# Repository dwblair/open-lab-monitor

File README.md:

open-lab-monitor
=================

### Overview

An open hardware microcontroller device for use in research and teaching laboratory settings, and as an independent sensing node.

### PCB

- Nice reference for MAGJACK options:
http://mbed.org/cookbook/Ethernet-RJ45 
- Nice reference for uSD breakout schematic, adafruit:
https://raw.github.com/adafruit/MicroSD-breakout-board/master/usdbreakout.png

### Code

Code for controlling the Open Lab Monitor device, the development and goals and applications of which are documented [here](https://github.com/Pioneer-Valley-Open-Science/pioneer-valley-open-science.github.com/issues/8).

The code consists of Arduino code to be loaded on an Arduino-based sensor platform, as well as a Processing and Python interface for interacting with the platform (e.g. plotting sensor values, downloading data as a CSV file). 

#### Notes on the Arduino Code

Some non-standard Arduino libraries are required, frozen versions of which can be found [here](https://github.com/dwblair/open-lab-monitor/tree/master/arduino/libraries).  Copy (or better yet, link) the folders under "libraries" to your "libraries" folder for your Arduino sketchbook:

* ThermistorLib (cversek's library for reading thermistor values) -- latest version found [here](https://github.com/cversek/umass-physics/tree/master/teis/arduino/ThermistorLib).
                                                                  
* SerialCommand (originally Steven Cogswell's slick library for parsing commands over serial)  -- check out his surly [blog post](http://husks.wordpress.com/2011/05/23/a-minimal-arduino-library-for-processing-serial-commands/); we are using the new and improved version hosted on github [here](https://github.com/kroimon/Arduino-SerialCommand)

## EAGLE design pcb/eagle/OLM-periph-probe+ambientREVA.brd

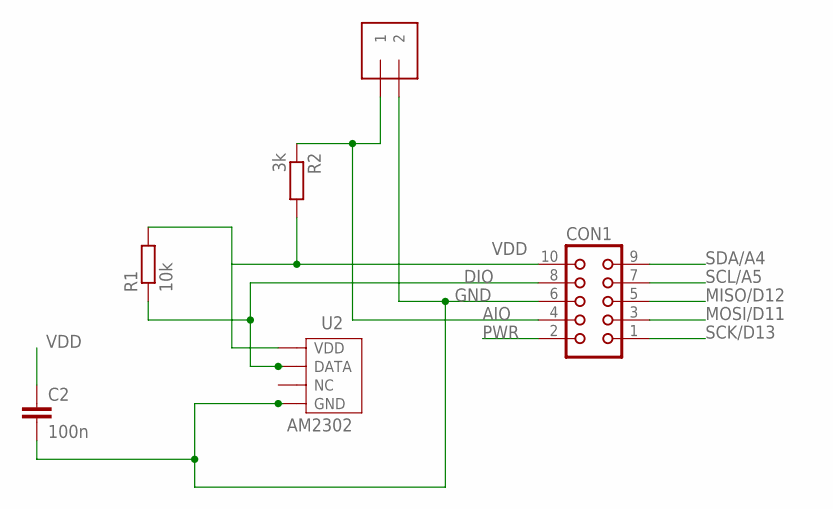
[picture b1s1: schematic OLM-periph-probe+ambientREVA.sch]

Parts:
C2: 100n; C025-024X044
CON1: CON10L
J1: 1X2-3.5MM
R1: 10k; 0204/7
R2: 3k; 0204/7
U2: AM2302

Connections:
AIO: CON1.4, J1.1, R2.1
DIO: CON1.8, R1.1, U2.P$2 (DATA)
GND: C2.2, CON1.6, J1.2, U2.P$4 (GND)
MISO/D12: CON1.5
MOSI/D11: CON1.3
PWR: CON1.2
SCK/D13: CON1.1
SCL/A5: CON1.7
SDA/A4: CON1.9
VDD: C2.1, CON1.10, R1.2, R2.2, U2.P$1 (VDD)

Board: 2 copper layers, 6 parts (0 on the bottom side), 4 nets, no tracks yet.

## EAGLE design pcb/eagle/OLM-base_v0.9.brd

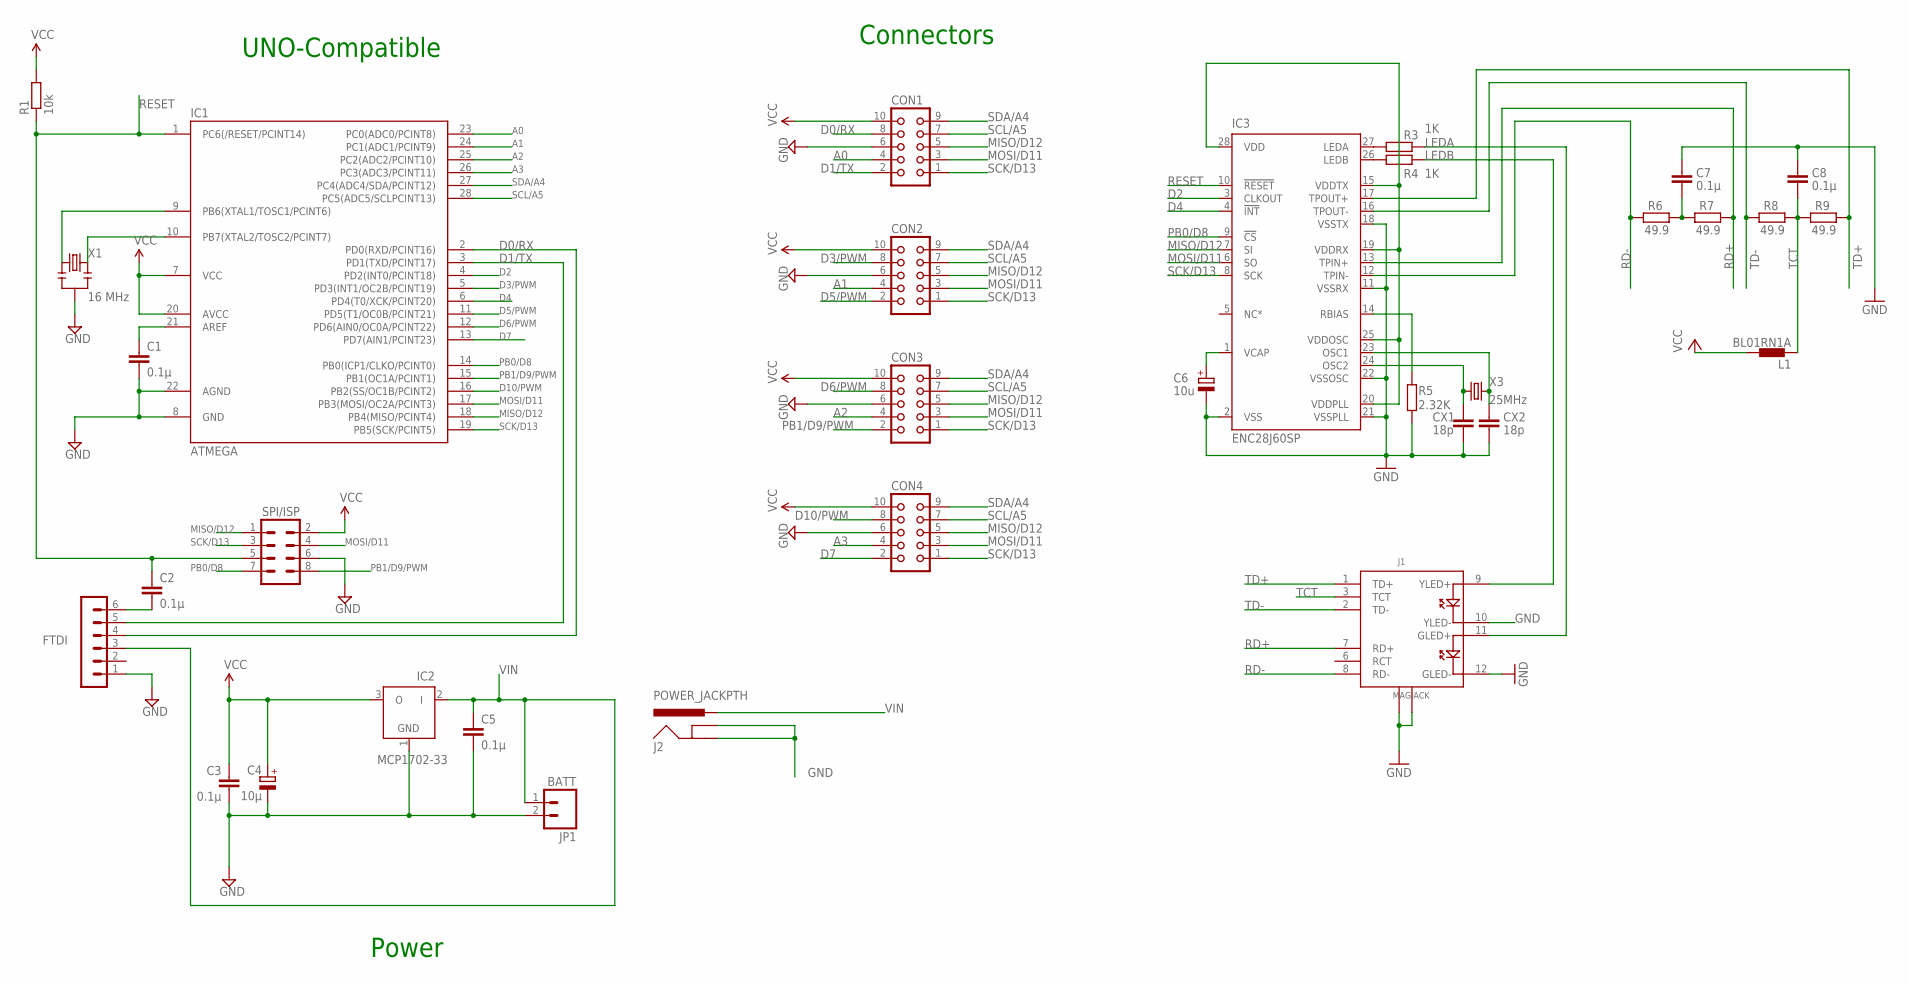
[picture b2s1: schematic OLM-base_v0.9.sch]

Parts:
C1, C2, C3, C5, C7, C8: 0.1µ; C025-024X044
C4: 10µ; E1,8-4
C6: 10u; E1,8-4
CON1, CON2, CON3, CON4: CON10L
CX1, CX2: 18p; C025-024X044
FTDI: FTDI; MA06-1
IC1: ATMEGA; DIL28-3
IC2: MCP1702-33; TO92
IC3: ENC28J60SP; DIL28-3
J1: MAGJACK
J2: POWER_JACKPTH; POWER_JACK_PTH
JP1: BATT; 1X02_LOCK_LONGPADS
L1: BL01RN1A
R1: 10k; 0204/7
R3, R4: 1K; 0204/7
R5: 2.32K; 0204/7
R6, R7, R8, R9: 49.9; 0204/7
SV1: SPI/ISP; MA04-2
X1: 16 MHz; RESONATOR-PTH
X3: 25MHz; HC49US

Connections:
A0: CON1.4, IC1.23 (PC0(ADC0/PCINT8))
A1: CON2.4, IC1.24 (PC1(ADC1/PCINT9))
A2: CON3.4, IC1.25 (PC2(ADC2/PCINT10))
A3: CON4.4, IC1.26 (PC3(ADC3/PCINT11))
D0/RX: CON1.8, FTDI.4, IC1.2 (PD0(RXD/PCINT16))
D1/TX: CON1.2, FTDI.5, IC1.3 (PD1(TXD/PCINT17))
D2: IC1.4 (PD2(INT0/PCINT18)), IC3.3 (CLKOUT)
D3/PWM: CON2.8, IC1.5 (PD3(INT1/OC2B/PCINT19))
D4: IC1.6 (PD4(T0/XCK/PCINT20)), IC3.4 (!INT)
D5/PWM: CON2.2, IC1.11 (PD5(T1/OC0B/PCINT21))
D6/PWM: CON3.8, IC1.12 (PD6(AIN0/OC0A/PCINT22))
D7: CON4.2, IC1.13 (PD7(AIN1/PCINT23))
D10/PWM: CON4.8, IC1.16 (PB2(SS/OC1B/PCINT2))
GND: C1.2, C3.2, C4.-, C5.2, C6.-, C7.1, C8.1, CON1.6, CON2.6, CON3.6, CON4.6, CX1.2, CX2.2, FTDI.1, IC1.8 (GND), IC1.22 (AGND), IC2.1 (GND), IC3.2 (VSS), IC3.11 (VSSRX), IC3.18 (VSSTX), IC3.21 (VSSPLL), IC3.22 (VSSOSC), J1.10 (YLED-), J1.12 (GLED-), J1.M1 (GND1), J1.M2 (GND2), J2.GND, J2.GNDBREAK, JP1.2, R5.2, SV1.6, X1.2
LEDA: J1.11 (GLED+), R3.2
LEDB: J1.9 (YLED+), R4.2
MISO/D12: CON1.5, CON2.5, CON3.5, CON4.5, IC1.18 (PB4(MISO/PCINT4)), IC3.7 (SI), SV1.1
MOSI/D11: CON1.3, CON2.3, CON3.3, CON4.3, IC1.17 (PB3(MOSI/OC2A/PCINT3)), IC3.6 (SO), SV1.4
unnamed: IC1.9 (PB6(XTAL1/TOSC1/PCINT6)), X1.1
unnamed: C1.1, IC1.21 (AREF)
unnamed: C2.2, FTDI.6
unnamed: IC1.10 (PB7(XTAL2/TOSC2/PCINT7)), X1.3
unnamed: IC3.27 (LEDA), R3.1
unnamed: IC3.26 (LEDB), R4.1
unnamed: C6.+, IC3.1 (VCAP)
unnamed: IC3.14 (RBIAS), R5.1
unnamed: CX1.1, IC3.24 (OSC2), X3.1
unnamed: CX2.1, IC3.23 (OSC1), X3.2
unnamed: C7.2, R6.2, R7.1
PB0/D8: IC1.14 (PB0(ICP1/CLKO/PCINT0)), IC3.9 (!CS), SV1.7
PB1/D9/PWM: CON3.2, IC1.15 (PB1(OC1A/PCINT1)), SV1.8
RD+: IC3.13 (TPIN+), J1.7 (RD+), R7.2
RD-: IC3.12 (TPIN-), J1.8 (RD-), R6.1
RESET: C2.1, IC1.1 (PC6(/RESET/PCINT14)), IC3.10 (!RESET), R1.1, SV1.5
SCK/D13: CON1.1, CON2.1, CON3.1, CON4.1, IC1.19 (PB5(SCK/PCINT5)), IC3.8 (SCK), SV1.3
SCL/A5: CON1.7, CON2.7, CON3.7, CON4.7, IC1.28 (PC5(ADC5/SCLPCINT13))
SDA/A4: CON1.9, CON2.9, CON3.9, CON4.9, IC1.27 (PC4(ADC4/SDA/PCINT12))
TCT: C8.2, J1.3 (TCT), L1.1, R8.2, R9.1
TD+: IC3.17 (TPOUT+), J1.1 (TD+), R9.2
TD-: IC3.16 (TPOUT-), J1.2 (TD-), R8.1
VCC: C3.1, C4.+, CON1.10, CON2.10, CON3.10, CON4.10, IC1.7 (VCC), IC1.20 (AVCC), IC2.3 (O), IC3.15 (VDDTX), IC3.19 (VDDRX), IC3.20 (VDDPLL), IC3.25 (VDDOSC), IC3.28 (VDD), L1.2, R1.2, SV1.2
VIN: C5.1, FTDI.3, IC2.2 (I), J2.PWR, JP1.1

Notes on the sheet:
UNO-Compatible
Connectors
Power

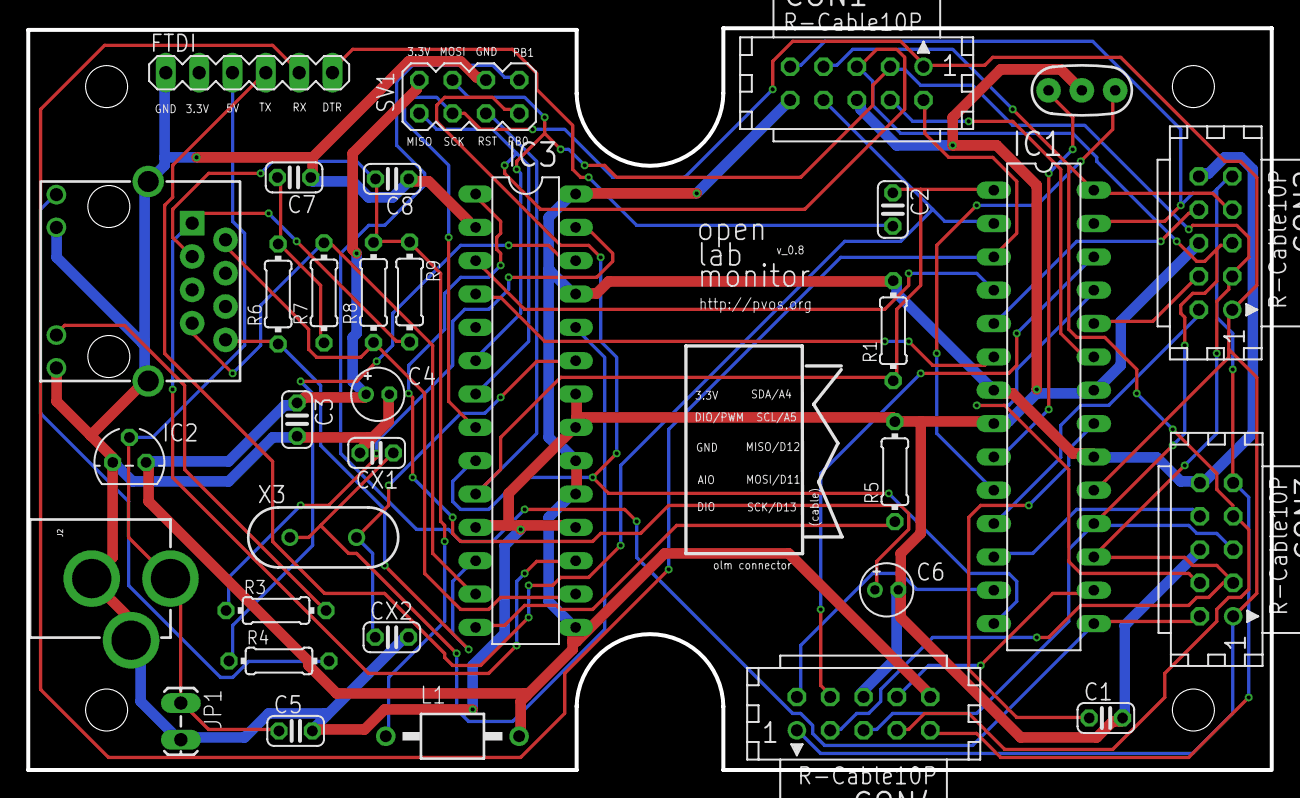
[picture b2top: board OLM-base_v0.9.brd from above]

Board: 2 copper layers, 94.7 x 56.5 mm, 33 parts (0 on the bottom side), 42 nets.

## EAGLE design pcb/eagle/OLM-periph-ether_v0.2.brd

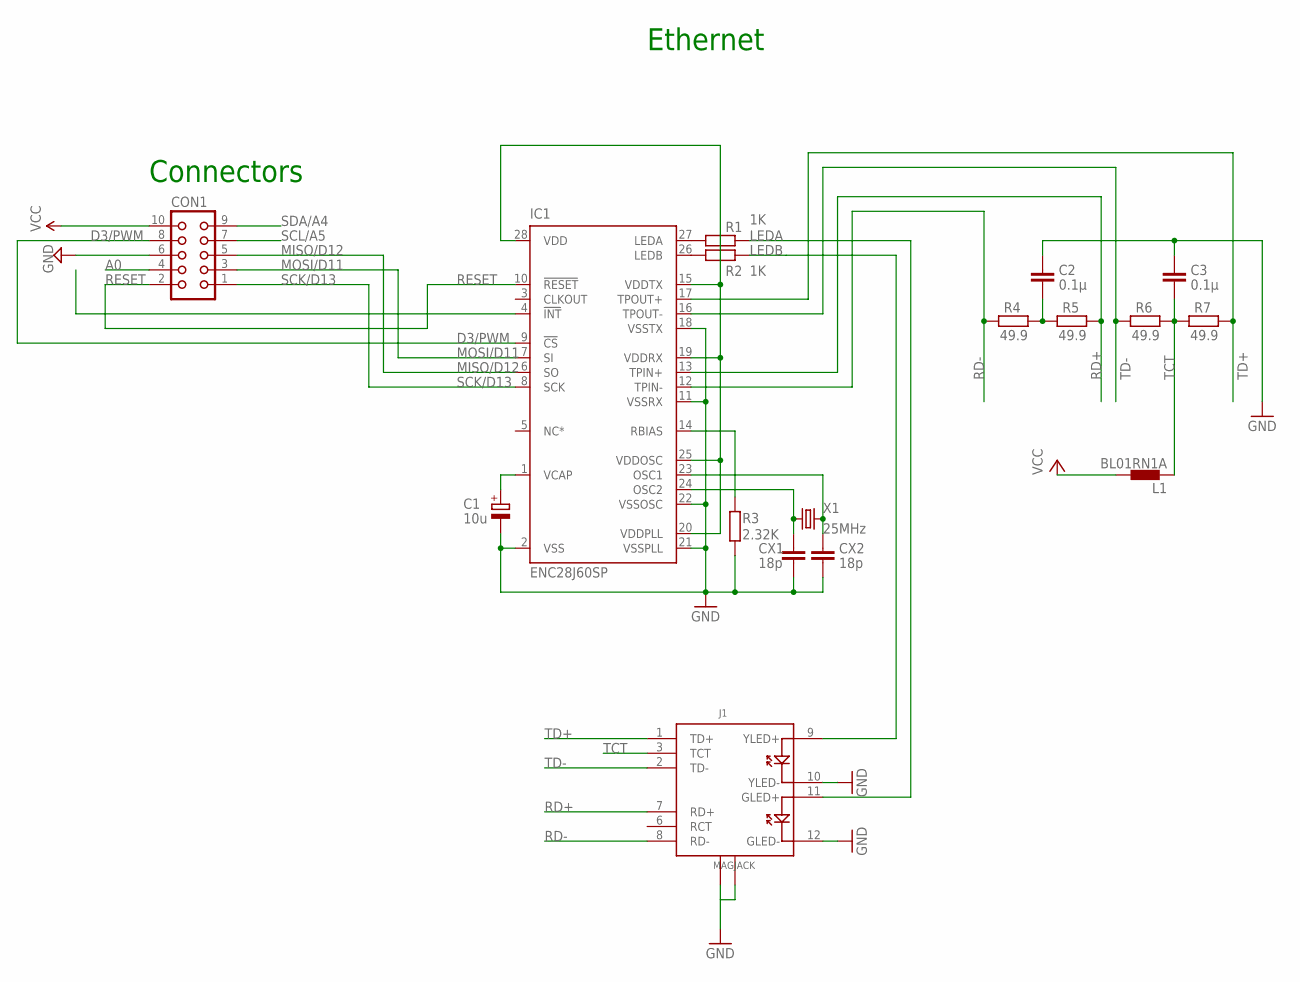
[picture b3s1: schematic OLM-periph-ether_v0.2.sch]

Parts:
C1: 10u; E1,8-4
C2, C3: 0.1µ; C025-024X044
CON1: CON10L
CX1, CX2: 18p; C025-024X044
IC1: ENC28J60SP; DIL28-3
J1: MAGJACK
L1: BL01RN1A
R1, R2: 1K; 0204/7
R3: 2.32K; 0204/7
R4, R5, R6, R7: 49.9; 0204/7
X1: 25MHz; HC49US

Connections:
A0: CON1.4
D3/PWM: CON1.8, IC1.9 (!CS)
GND: C1.-, C2.1, C3.1, CON1.6, CX1.2, CX2.2, IC1.2 (VSS), IC1.11 (VSSRX), IC1.18 (VSSTX), IC1.21 (VSSPLL), IC1.22 (VSSOSC), J1.12 (GLED-), J1.M1 (GND1), J1.M2 (GND2), R3.2
LEDA: J1.11 (GLED+), R1.2
LEDB: J1.9 (YLED+), R2.2
MISO/D12: CON1.5, IC1.6 (SO)
MOSI/D11: CON1.3, IC1.7 (SI)
unnamed: IC1.27 (LEDA), R1.1
unnamed: IC1.26 (LEDB), R2.1
unnamed: C1.+, IC1.1 (VCAP)
unnamed: IC1.14 (RBIAS), R3.1
unnamed: CX1.1, IC1.24 (OSC2), X1.1
unnamed: CX2.1, IC1.23 (OSC1), X1.2
unnamed: C2.2, R4.2, R5.1
RD+: IC1.13 (TPIN+), J1.7 (RD+), R5.2
RD-: IC1.12 (TPIN-), J1.8 (RD-), R4.1
RESET: CON1.2, IC1.10 (!RESET)
SCK/D13: CON1.1, IC1.8 (SCK)
SCL/A5: CON1.7
SDA/A4: CON1.9
TCT: C3.2, J1.3 (TCT), L1.1, R6.2, R7.1
TD+: IC1.17 (TPOUT+), J1.1 (TD+), R7.2
TD-: IC1.16 (TPOUT-), J1.2 (TD-), R6.1
VCC: CON1.10, IC1.15 (VDDTX), IC1.19 (VDDRX), IC1.20 (VDDPLL), IC1.25 (VDDOSC), IC1.28 (VDD), L1.2

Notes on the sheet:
Ethernet
Connectors

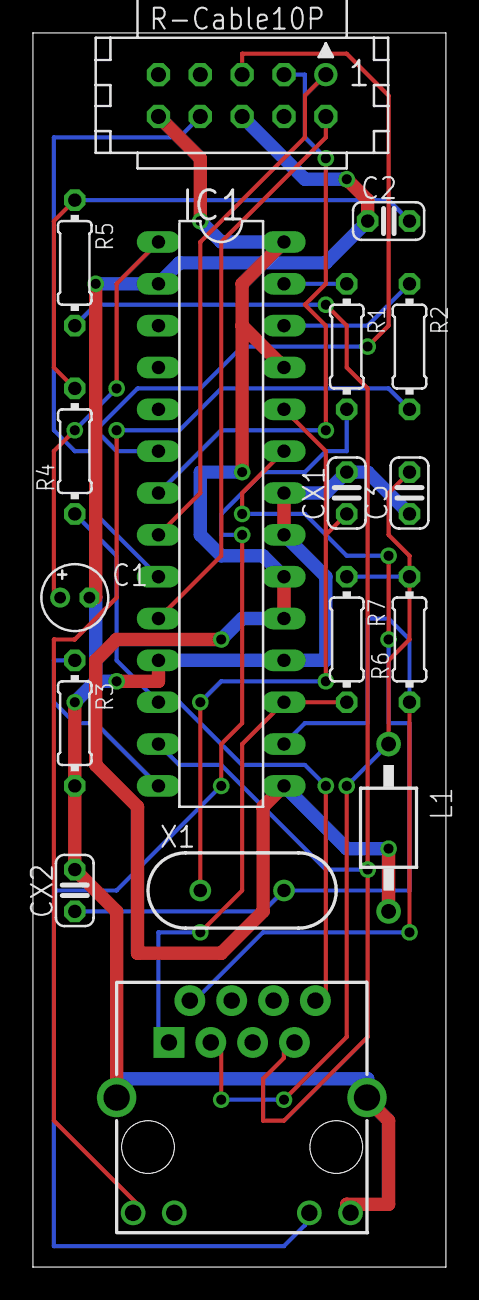
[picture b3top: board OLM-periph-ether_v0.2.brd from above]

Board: 2 copper layers, 25.1 x 74.9 mm, 17 parts (0 on the bottom side), 21 nets.

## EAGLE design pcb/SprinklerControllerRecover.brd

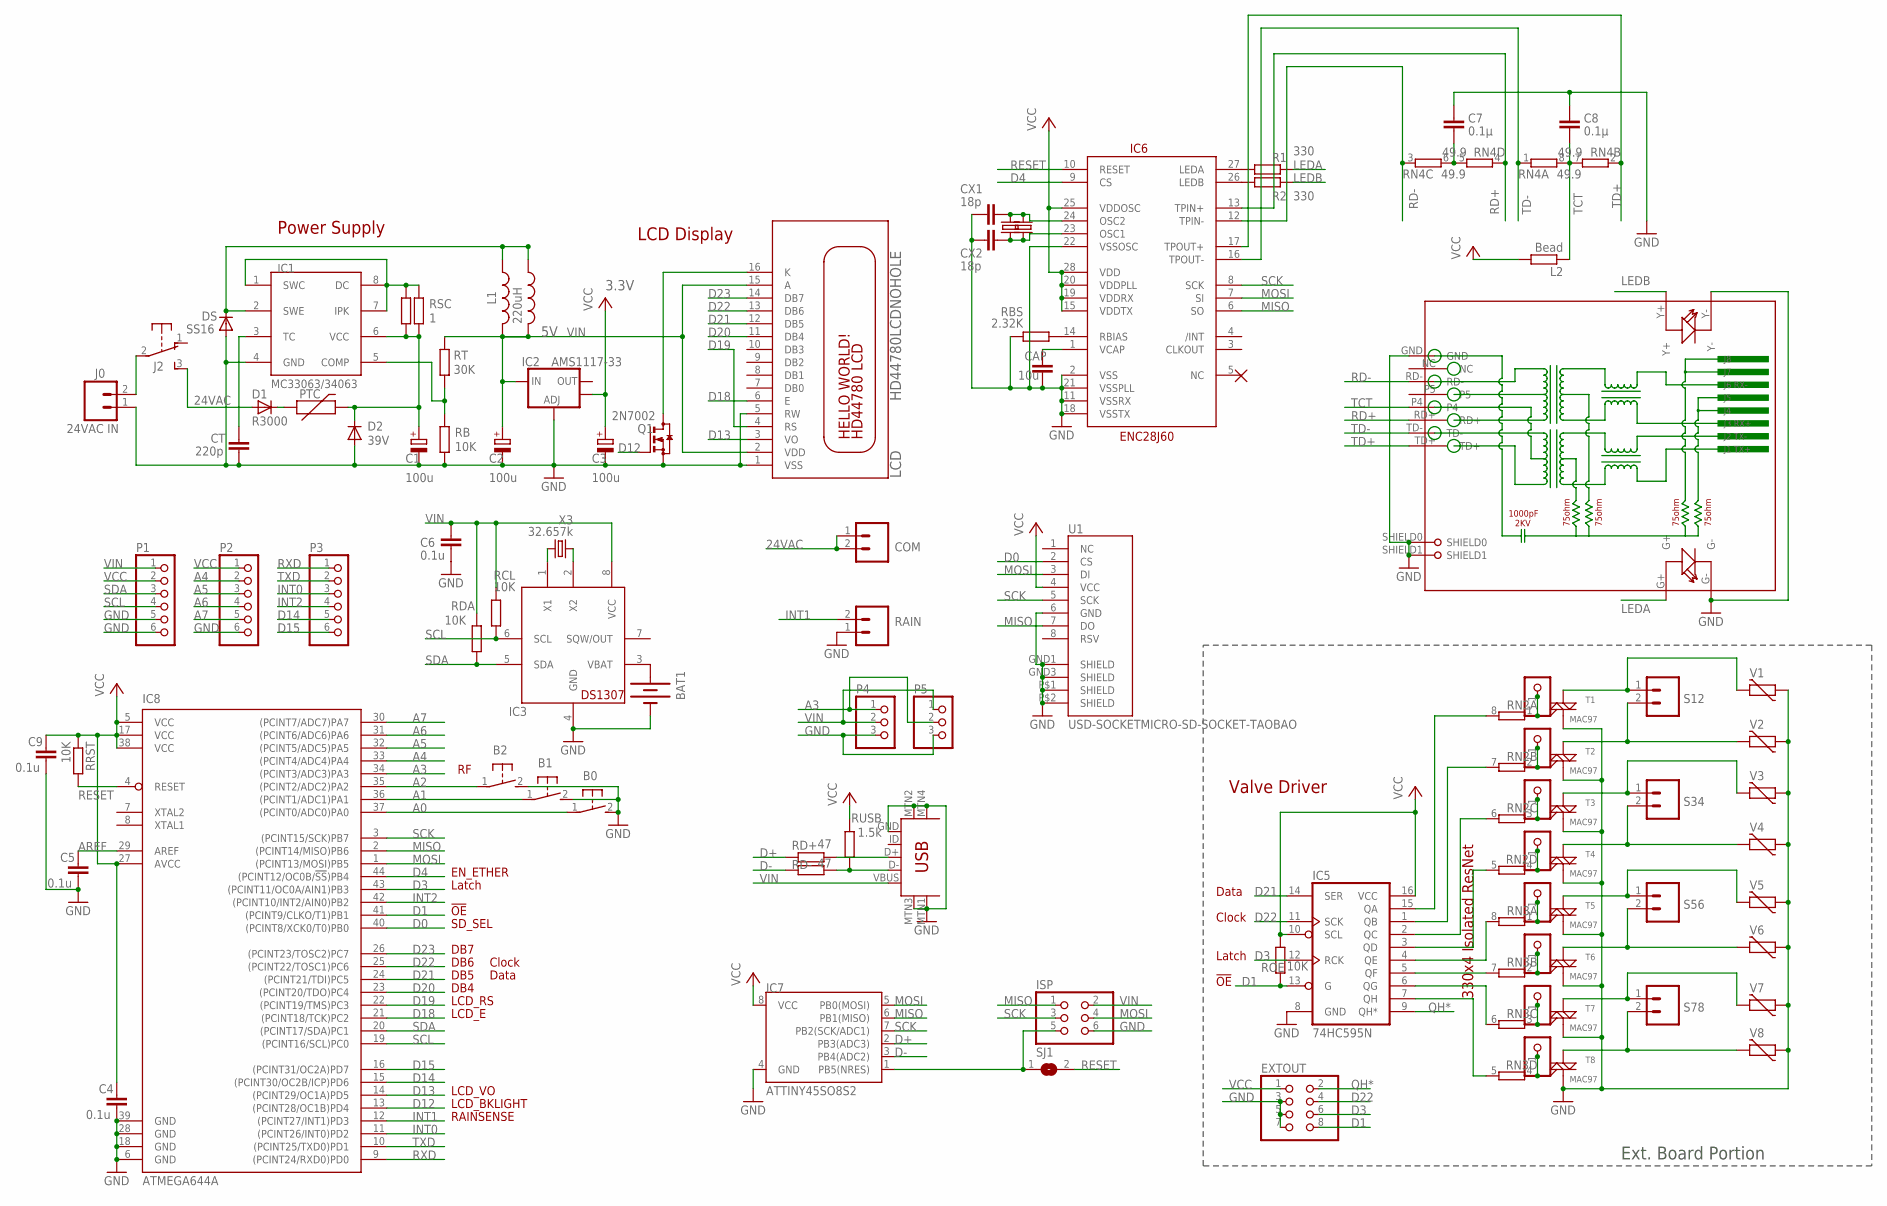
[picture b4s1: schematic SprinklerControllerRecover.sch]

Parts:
B0, B1, B2: 31-XX; B3F-31XX
BAT1: BATTERYBATTERY_12MM_SMT; BATTCON_12MM_SMT
C1: 100u; E3,5-8
C2, C3: 100u; E2,5-5
C4, C5, C6, C9: 0.1u; C0805
C7, C8: 0.1µ; C0805
CAP: 10u; C0805
COM: M025MM; SCREWTERMINAL-5MM-2
CT: 220p; C0805
CX1, CX2: 18p; C0805
D1: R3000; DO41-7.6
D2: 39V; DO41-7.6
DS: SS16; DO214AC
EXTOUT: PINHD-2X4; 2X04
IC1: MC34063; SO08
IC2: AMS1117-33; SOT223
IC3: DS1307; SO08
IC5: 74HC595N; SO16
IC6: ENC28J60; SOIC28WLONG
IC7: ATTINY45SO8S2; SO8S2
IC8: ATMEGA644A; TQFP44
ISP: PINHD-2X3; 2X03
J0: 24VAC IN; SCREWTERMINAL-5MM-2
J2: EG1206
JP2, JP3, JP4, JP5, JP6, JP7, JP8, JP9: PINHD-1X1CB; 1X01-CLEANBIG
L1: 220uH; 6000-XXXX-RC
L2: Bead; R0805
L3: 220uH; SRU1038
LCD: HD44780LCDNOHOLE; LCD1602A
P1, P2, P3: PINHD-1X6CLEAN; 1X06-CLEAN
P4, P5: PINHD-1X3; 1X03
PTC: PTC
Q1: 2N7002; SOT23
R1, R2: 330; R0805
RAIN: M025MM; SCREWTERMINAL-5MM-2
RB: 10K; R0805
RBS: 2.32K; R0805
RCL: 10K; R0805
RD+: 47; R0805
RD-: 47; R0805
RDA: 10K; R0805
RJ1: HR911105A
RN2, RN3: 4R-NEXB38V; EXB38V
RN4: 49.9; EXB38V
ROE: 10K; R0805
RRST: 10K; R0805
RSC: 1; R0805
RSC1: 1.0; R0805
RT: 30K; R0805
RUSB: 1.5k; R0805
S12, S34, S56, S78: M025MM; SCREWTERMINAL-5MM-2
SJ1: SJ
T1, T2, T3, T4, T5, T6, T7, T8: MAC97; SOT223
U1: USD-SOCKETMICRO-SD-SOCKET-TAOBAO; MICRO-SD-SOCKET-TAOBAO
U$1: USB-MINIB-5PIN; USB-MINIB
V1, V2, V3, V4, V5, V6, V7, V8: MOV; R-5
X2A: 25MHz; CRYSTAL-SMD-10.5X4.8-2PIN
X2A1: 25MHz; HC49US
X3: 32.657k; TC26H

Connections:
24VAC: COM.1, COM.2, D1.A, J2.3 (S)
A0: B0.1, IC8.37 ((PCINT0/ADC0)PA0)
A1: B1.1, IC8.36 ((PCINT1/ADC1)PA1)
A2: B2.1, IC8.35 ((PCINT2/ADC2)PA2)
A3: IC8.34 ((PCINT3/ADC3)PA3), P4.1, P5.2
A4: IC8.33 ((PCINT4/ADC4)PA4), P2.2
A5: IC8.32 ((PCINT5/ADC5)PA5), P2.3
A6: IC8.31 ((PCINT6/ADC6)PA6), P2.4
A7: IC8.30 ((PCINT7/ADC7)PA7), P2.5
AREF: C5.1, IC8.29 (AREF)
D0: IC8.40 ((PCINT8/XCK0/T0)PB0), U1.2 (CS)
D1: EXTOUT.8, IC5.13 (G), IC8.41 ((PCINT9/CLKO/T1)PB1), ROE.1
D3: EXTOUT.6, IC5.12 (RCK), IC8.43 ((PCINT11/OC0A/AIN1)PB3)
D4: IC6.9 (CS), IC8.44 ((PCINT12/OC0B/!SS!)PB4)
D12: IC8.13 ((PCINT28/OC1B)PD4), Q1.1 (G)
D13: IC8.14 ((PCINT29/OC1A)PD5), LCD.3 (VO)
D14: IC8.15 ((PCINT30/OC2B/ICP)PD6), P3.5
D15: IC8.16 ((PCINT31/OC2A)PD7), P3.6
D18: IC8.21 ((PCINT18/TCK)PC2), LCD.6 (E)
D19: IC8.22 ((PCINT19/TMS)PC3), LCD.4 (RS)
D20: IC8.23 ((PCINT20/TDO)PC4), LCD.11 (DB4)
D21: IC5.14 (SER), IC8.24 ((PCINT21/TDI)PC5), LCD.12 (DB5)
D22: EXTOUT.4, IC5.11 (SCK), IC8.25 ((PCINT22/TOSC1)PC6), LCD.13 (DB6)
D23: IC8.26 ((PCINT23/TOSC2)PC7), LCD.14 (DB7)
D+: IC7.2 (PB3(ADC3)), RD+.1
D-: IC7.3 (PB4(ADC2)), RD-.1
GND: B0.2 (S), B1.2 (S), B2.2 (S), BAT1.P$1 (-), C1.-, C2.-, C3.-, C4.2, C5.2, C6.2, C7.1, C8.1, C9.2, CAP.2, CT.2, CX1.2, CX2.2, D2.A, DS.A, EXTOUT.3, EXTOUT.5, EXTOUT.7, IC1.4 (GND), IC2.1 (ADJ), IC3.4 (GND), IC5.8 (GND), IC6.2 (VSS), IC6.11 (VSSRX), IC6.18 (VSSTX), IC6.21 (VSSPLL), IC6.22 (VSSOSC), IC7.4 (GND), IC8.6 (GND), IC8.18 (GND), IC8.28 (GND), IC8.39 (GND), ISP.6, J0.1, LCD.1 (VSS), LCD.5 (RW), P1.5, P1.6, P2.6, P4.3, P5.3, Q1.2 (S), RAIN.1, RB.2, RBS.1, RJ1.G-, RJ1.GND, RJ1.SHIELD0, RJ1.SHIELD1, RJ1.Y-, T1.1 (M1), T2.1 (M1), T3.1 (M1), T4.1 (M1), T5.1 (M1), T6.1 (M1), T7.1 (M1), T8.1 (M1), U1.6 (GND), U1.GND1 (SHIELD), U1.GND3 (SHIELD), U1.P$1 (SHIELD), U1.P$2 (SHIELD), U$1.GND, U$1.MTN1 (MTN2), U$1.MTN2 (MTN3), U$1.MTN3 (MTN1), U$1.MTN4, V1.1, V2.1, V3.1, V4.1, V5.1, V6.1, V7.1, V8.1
INT0: IC8.11 ((PCINT26/INT0)PD2), P3.3
INT1: IC8.12 ((PCINT27/INT1)PD3), RAIN.2
INT2: IC8.42 ((PCINT10/INT2/AIN0)PB2), P3.4
LEDA: R1.2, RJ1.G+
LEDB: R2.2, RJ1.Y+
MISO: IC6.6 (SO), IC7.6 (PB1(MISO)), IC8.2 ((PCINT14/MISO)PB6), ISP.1, U1.7 (DO)
MOSI: IC6.7 (SI), IC7.5 (PB0(MOSI)), IC8.1 ((PCINT13/MOSI)PB5), ISP.4, U1.3 (DI)
unnamed: D1.C, PTC.P$1 (1)
unnamed: JP2.1, RN2.1, T1.3 (G)
unnamed: IC5.5 (QF), RN3.7 (2)
unnamed: IC5.6 (QG), RN3.6 (2)
unnamed: J0.2, J2.2
unnamed: IC5.7 (QH), RN3.5 (2)
unnamed: C1.+, D2.C, IC1.6 (VCC), PTC.P$2 (2), RSC.2, RSC1.2
unnamed: IC5.4 (QE), RN3.8 (2)
unnamed: IC5.3 (QD), RN2.5 (2)
unnamed: IC5.2 (QC), RN2.6 (2)
unnamed: IC5.1 (QB), RN2.7 (2)
unnamed: IC5.15 (QA), RN2.8 (2)
unnamed: JP3.1, RN2.2 (1), T2.3 (G)
unnamed: S12.1, T1.4 (M2), V1.2
unnamed: S12.2, T2.4 (M2), V2.2
unnamed: S34.1, T3.4 (M2), V3.2
unnamed: JP4.1, RN2.3 (1), T3.3 (G)
unnamed: S34.2, T4.4 (M2), V4.2
unnamed: JP5.1, RN2.4 (1), T4.3 (G)
unnamed: S56.1, T5.4 (M2), V5.2
unnamed: S56.2, T6.4 (M2), V6.2
unnamed: S78.1, T7.4 (M2), V7.2
unnamed: S78.2, T8.4 (M2), V8.2
unnamed: JP6.1, RN3.1, T5.3 (G)
unnamed: JP7.1, RN3.2 (1), T6.3 (G)
unnamed: JP8.1, RN3.3 (1), T7.3 (G)
unnamed: JP9.1, RN3.4 (1), T8.3 (G)
unnamed: IC6.27 (LEDA), R1.1
unnamed: BAT1.P$2 (+), IC3.3 (VBAT)
unnamed: IC6.26 (LEDB), R2.1
unnamed: RD+.2, U$1.D+
unnamed: CAP.1, IC6.1 (VCAP)
unnamed: IC1.1 (SWC), IC1.7 (IPK), IC1.8 (DC), RSC.1, RSC1.1
unnamed: CX1.1, IC6.24 (OSC2), X2A.P$2 (2), X2A1.2
unnamed: CX2.1, IC6.23 (OSC1), X2A.P$1 (1), X2A1.1
unnamed: RD-.2, RUSB.1, U$1.D-
unnamed: DS.C, IC1.2 (SWE), L1.1, L3.1
unnamed: IC3.1 (X1), X3.1
unnamed: CT.1, IC1.3 (TC)
unnamed: IC3.2 (X2), X3.2
unnamed: IC7.1 (PB5(NRES)), ISP.5, SJ1.1
unnamed: C7.2, RN4.5 (2), RN4.6 (2)
unnamed: IC1.5 (COMP), RB.1, RT.2
unnamed: LCD.16 (K), Q1.3 (D)
unnamed: IC6.14 (RBIAS), RBS.2
QH*: EXTOUT.2, IC5.9 (QH*)
RD+: IC6.13 (TPIN+), RJ1.RD+, RN4.4 (1)
RD-: IC6.12 (TPIN-), RJ1.RD-, RN4.3 (1)
RESET: IC6.10 (RESET), IC8.4 (RESET), RRST.2, SJ1.2
RXD: IC8.9 ((PCINT24/RXD0)PD0), P3.1
SCK: IC6.8 (SCK), IC7.7 (PB2(SCK/ADC1)), IC8.3 ((PCINT15/SCK)PB7), ISP.3, U1.5 (SCK)
SCL: IC3.6 (SCL), IC8.19 ((PCINT16/SCL)PC0), P1.4, RCL.2
SDA: IC3.5 (SDA), IC8.20 ((PCINT17/SDA)PC1), P1.3, RDA.2
TCT: C8.2, L2.1, RJ1.P4, RN4.7 (2), RN4.8 (2)
TD+: IC6.17 (TPOUT+), RJ1.TD+, RN4.2 (1)
TD-: IC6.16 (TPOUT-), RJ1.TD-, RN4.1
TXD: IC8.10 ((PCINT25/TXD0)PD1), P3.2
VCC: C3.+, C4.1, C9.1, EXTOUT.1, IC2.4 (OUT), IC5.10 (SCL), IC5.16 (VCC), IC6.15 (VDDTX), IC6.19 (VDDRX), IC6.20 (VDDPLL), IC6.25 (VDDOSC), IC6.28 (VDD), IC7.8 (VCC), IC8.5 (VCC), IC8.17 (VCC), IC8.27 (AVCC), IC8.38 (VCC), L2.2, P1.2, P2.1, ROE.2, RRST.1, RUSB.2, U1.4 (VCC)
VIN: C2.+, C6.1, IC2.3 (IN), IC3.8 (VCC), ISP.2, L1.2, L3.2, LCD.2 (VDD), LCD.15 (A), P1.1, P4.2, P5.1, RCL.1, RDA.1, RT.1, U$1.VBUS

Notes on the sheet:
Power Supply
Valve Driver
Data
Clock
Latch
DB4
330x4 Isolated ResNet
LCD Display
EN_ETHER
3.3V
DB7
LCD_E
LCD_RS
DB6
DB5
Ext. Board Portion
!OE
RAINSENSE
LCD_BKLIGHT
LCD_VO
SD_SEL

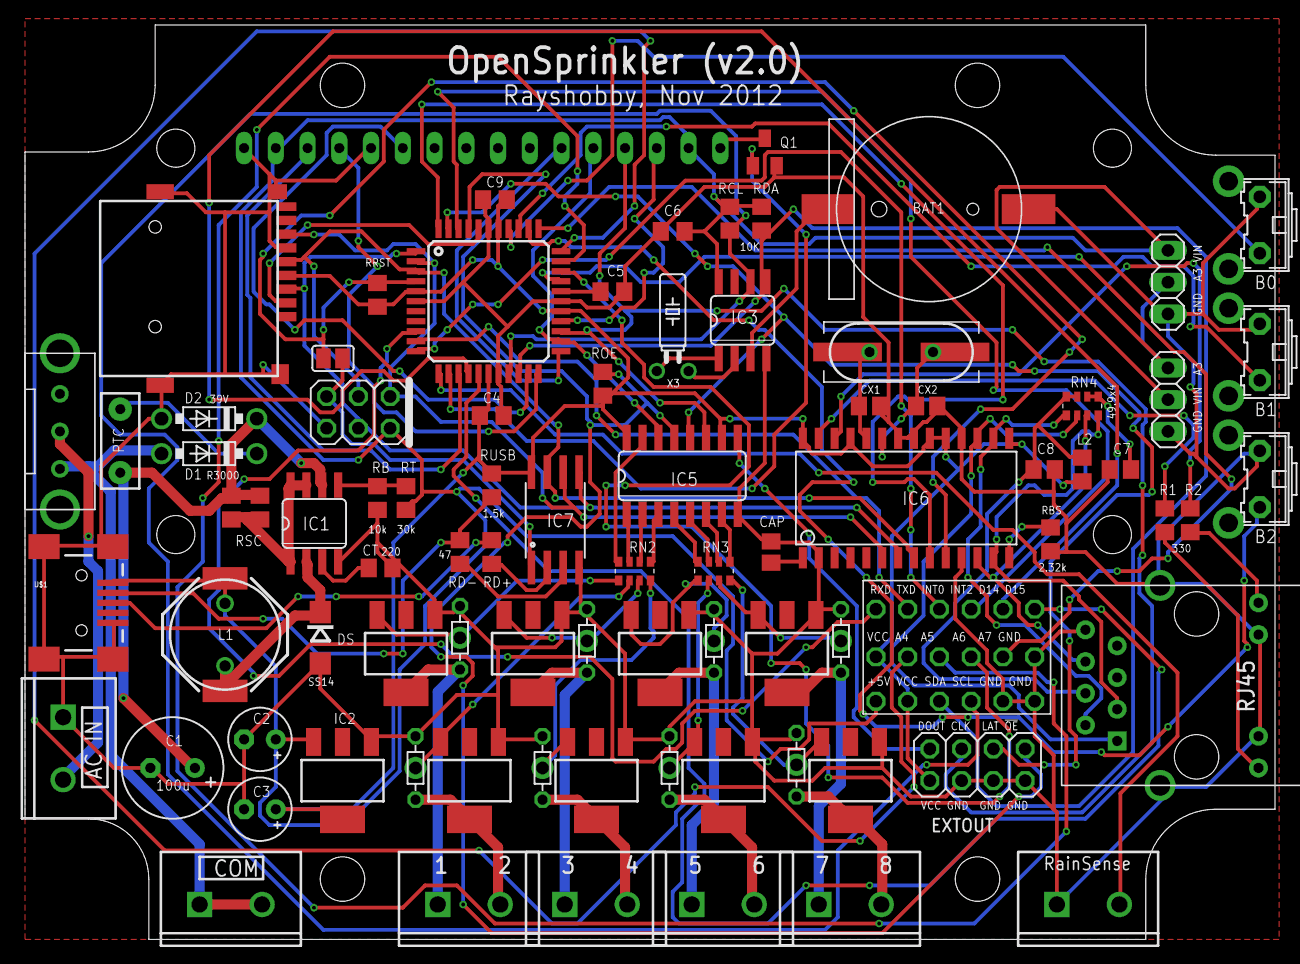
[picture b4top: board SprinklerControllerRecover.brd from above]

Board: 2 copper layers, 100.0 x 73.2 mm, 96 parts (0 on the bottom side), 93 nets.

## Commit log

2012-09-16 test commit 1
2012-09-16 adding the new folders
2012-09-16 added folders
2012-09-16 edited readme to include directions for finding the necessary libraries related to the arduino
2012-09-17 testing collaborative dev
2012-09-17 fixed formatting and changed some object names
2012-09-17 added a few add-on arduino library dependencies
2012-09-17 Update README.md
    added new info on how to install the non-standard Arduino libraries
2012-09-17 updated library to version hosted at https://github.com/kroimon/Arduino-SerialCommand
2012-09-17 Update arduino/Pressure_Thermistor_LCD_combo/Pressure_Thermistor_LCD_combo.ino
    integrated support for SerialCommand parsing library;
    added UPDATE command which prints the current sensor data to the serial port
2012-09-17 fixed some bugs that prevent compiling
2013-01-08 test
2013-01-09 added files
2013-01-16 arduino
2013-01-16 changed pcb around
2013-01-16 grooming
2013-01-16 auto commit
2013-01-17 Add .gitignore
2013-01-17 Remove gitpush.sh
2013-01-17 Changes with Ben
2013-01-17 reconfigured OLM.sch; reconfigured ENC symbol.
2013-01-18 v3 of OLM-CONNECTOR; built out ethernet
2013-01-20 fixes.
2013-01-20 the ingredients
2013-01-20 Current status
2013-01-21 More work with Ben
2013-01-21 Add more packages
2013-01-21 connected atmel pins to connectors, ethernet, uSD.
2013-01-21 added warning re: renaming LEDs
2013-01-22 added external connector charge status indication LEDs; made sure that pin D8 went to CS on ethernet controller in order to ensure compatibility with Ethercard library defaults
2013-01-22 added tssop20.fp footprint to packages
2013-01-22 adding in the 8-bit i2c expander, and reconfiguring pins accordingly ...
2013-01-23 finished laying out pins, incorporating I/O expander. 6 connectors now.
2013-01-23 Regenerated PNG image of schematic.
2013-01-23 rearranged pins in order to control INT on I/O Expander
2013-01-23 added PNG image
2013-02-02 rearranged pins on connectors to allow for two MCU DIO pins on each connector; redistributed I/O expander pins accordingly. one connector maintains two PWM digital pins (in case want to use it to dri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
2013-02-02 added SEPIC / bomb
2013-02-02 renamed some pins on the SEPIC, added some footprints
2013-02-02 added external LED option for MCU / TX / RX / 13 LEDs
2013-02-17 deleted SEPIC and LDO; created step-down part TPS6205xx
2013-04-03 cleaned up
2013-04-07 picture
2013-04-23 now based on through-hole jeenode v 6
2013-04-24 changed connectors
2013-04-26 started working on eagle
2013-04-27 reorganized
2013-04-28 made 'base' version
2013-04-28 added images
2013-05-02 layout of board + ethernet
2013-05-02 changed logo
2013-05-02 fixed logo
2013-05-02 made pic
2013-05-02 changed image resolution
2013-05-02 new version, fixed schematic
2013-05-02 changed schematic
2013-05-02 fixed graphics
2013-05-02 pic of schematic
2013-05-02 flipped ic3
2013-05-02 exported graphic
2013-05-02 minor fixes
2013-05-02 changed output for smart-prototyping
2013-05-02 added gerber files
2013-05-11 changed OLM connector topology; created peripheral
2013-05-20 added RTC
2013-05-26 placed reva
2013-05-26 added pngs
2013-05-26 added peripheral
2013-05-26 fixed terminal

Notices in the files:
parts and their libraries:
SparkFun-Connectors: Licensing: CC v3.0 Share-Alike You are welcome to use this library for commercial purposes.
